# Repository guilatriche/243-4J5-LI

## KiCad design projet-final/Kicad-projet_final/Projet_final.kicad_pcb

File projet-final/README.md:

# Projet Final : Infrastructure de Télémétrie - Poste 07 (Centrale Thermique)
**Cours 243-4J5-LI | Hydro-Limoilou**

## 📖 Contexte du Projet
Ce projet simule le déploiement de l'infrastructure de télémétrie pour **Hydro-Limoilou**. L'objectif est de surveiller les conditions opérationnelles (climat, sécurité, alimentation) de 8 sites de distribution d'énergie. 

Le **Poste 07**, simulant une **Centrale Thermique**, est responsable de son propre répéteur RF, de ses capteurs, de son courtier MQTT local (Raspberry Pi 5) et de son écran de monitoring tactile. Un serveur central (VM gérée par l'enseignant) agrège les données via une convention de topics standardisée.

---

## 🛠️ Matériel & Capteurs
- **Contrôleur Principal** : LilyGO T-SIM7600G-H (ESP32 avec modem LTE)
- **Interface Tactile** : Raspberry Pi 5 + Écran officiel 7"
- **Capteurs (I2C)** :
  - **BME280** : Température, Humidité et Pression atmosphérique.
  - **BH1750** : Intensité lumineuse (Lux) pour détection d'intrusion.
- **Sécurité (GPIO)** :
  - **Capteur PIR** : Détection de mouvement infrarouge.
- **Actuateurs** :
  - 2 LEDs de statut (Contrôlables via MQTT).

---

## 📐 Conception Matérielle (PCB)
Le shield PCB pour l'ESP32 a été conçu sous KiCad pour assurer une connectivité fiable et robuste des capteurs.

### Livrables de Conception (Dossier `/kicad`)
- **Schéma Électrique** : `shield.kicad_sch` (Validé par ERC)
- **Design du PCB** : `shield.kicad_pcb` (Validé par DRC, 2 couches)
- **Fichiers de Fabrication** : Dossier incluant les **Gerbers** (RS-274X) et le **BOM** (Bill of Materials).

### Consultation Rapide (Dossier `/docs`)
- **Schéma de principe** : [schéma_électrique.pdf](./docs/schéma_électrique.pdf)
- **Vue du montage** : [Photo_breadboard.jpeg](./docs/Photo_breadboard.jpeg)
- **Vidéo du scénario 1 - Démonstration de l'installation** : [Scénario_1_Présentation.MP4](./docs/Scénario%201%20-%20Présentation.MP4)
- **Vidéo du scénario 2 - Démonstration des alarmes** : [Scénario_2_Alarmes.MP4](./docs/Scénario%202%20-%20Alarmes.MP4)
- **Vidéo du scénario 3 - Démonstration du lien de secours** : [Scénario_3_Lien de secours.MP4](./docs/Scénario%203%20-%20Lien%20de%20secours.MP4)

---

## 🔌 Schéma de Câblage & Connexions
Le nœud capteur utilise un LilyGO T-SIM7600G-H. Voici l'assignation des broches (Pinout) utilisée pour le montage :

### 1. Bus I2C (Capteurs environnementaux)
*Partagé entre le BME280 et le BH1750 (Adresses 0x76 et 0x23).*
- **SDA** : GPIO 21
- **SCL** : GPIO 22
- **VCC** : 3.3V
- **GND** : Ground

### 2. Sécurité & Indicateurs
- **Capteur PIR (Mouvement)** : GPIO 32 (Entrée digitale)
- **LED 1 (Statut)** : GPIO 14 (Sortie via résistance 220Ω)
- **LED 2 (Alerte)** : GPIO 13 (Sortie via résistance 220Ω)

### 3. Gestion Énergie & Modem (Interne LilyGO)
- **Batterie ADC** : GPIO 35 (Pont diviseur interne pour mesure de tension)
- **Modem TX/RX** : GPIO 26 / 27
- **Modem Power Key** : GPIO 4
- **Board Power On** : GPIO 12 (Doit être HIGH pour alimenter les périphériques)

---

## 🚀 Fonctionnalités Clés

- **Surveillance & IA** : Publication des données environnementales et génération d'un diagnostic technique en langage naturel (IA LLM Groq) toutes les 2 minutes.
- **Sécurité Temps Réel** : Alarmes critiques (mouvement et intrusion porte) publiées en moins de 1 seconde avec QoS 1.
- **Connectivité Hybride** : Basculement automatique (Failover) entre le WiFi (Lien principal) et le réseau LTE (Lien de secours WAN privé).
- **Interface IHM** : HUD Pygame tactile sur le Pi 5 avec gestion des alarmes (verrouillage visuel et acquittement manuel).

---

## 🛠 Architecture MQTT & Contrat de Données

Le système respecte strictement la convention de topics de Hydro-Limoilou. Tous les topics sont obligatoirement préfixés par : `hydro-limoilou/poste-07/`.

| Catégorie | Topic (Suffixe) | QoS | Rétention | Description |
| :--- | :--- | :--- | :--- | :--- |
| **Télémétrie** | `telemetry/{capteur}` | 0 | Non | Mesures périodiques (10s) |
| **Statut** | `status` | 0 | Oui | État du nœud (Uptime, RSSI, Batterie) |
| **Statut IA** | `status/llm` | 0 | Oui | Diagnostic généré par l'IA (120s) |
| **Alarmes** | `alarm/{type}` | 1 | Non | Évènements : `motion`, `door` |
| **Actuateurs**| `actuators/{nom}` | 0 | Non | Commandes descendantes (VM → site) |

### 📊 Format des Payloads (JSON)
Les payloads sont minifiés et incluent obligatoirement un timestamp Unix.
- **Télémétrie** : `{"value": 22.4, "unit": "C", "ts": 1778526188}`
- **Alarmes** : `{"level": "critical", "value": 2500, "unit": "lux", "ts": 1778526188}`
- **Statut** : `{"uptime": 3600, "rssi": -67, "link": "wifi", "battery_v": 3.92, "ts": 1778526188}`

---

## 🔒 Exposition & Sécurité
Le courtier Mosquitto local du Pi 5 est accessible au serveur central via un **Tunnel Cloudflare** sécurisé.

- **URL de connexion** : `wss://mqtt.gretier.xyz:443/mqtt`
- **Username** : `central`
- **Password** : `<TRANSMIS_VIA_CANAL_SECURISE>` (Identifiants restreints par ACL)
- **Contrôle d'Accès (ACL)** : L'utilisateur central dispose d'un accès en **lecture seule** sur le site, sauf pour le dossier `/actuators/` où l'écriture est permise.

---

## 🧪 Procédure de Démonstration (Scénarios de Test)

### Scénario 1 : Fonctionnement Nominal -> **RÉSULTAT : PASSÉ ✅**
1.  Démarrer l'ESP32 et l'interface tactile.
2.  Vérifier sur l'interface que les jauges de température et humidité se mettent à jour toutes les 10 secondes.
3.  Confirmer sur le tableau de bord central (VM) la réception des données avec le bon `site-id`.

### Scénario 2 : Déclenchement d'Alarme -> **RÉSULTAT : PASSÉ ✅**
1.  Simuler une intrusion en passant la main devant le capteur PIR ou en éclairant brusquement le BH1750.
2.  **Résultat attendu** : L'interface tactile passe immédiatement en mode alerte (clignotement rouge). Un message avec `QoS 1` est publié sur `alarm/motion` ou `alarm/door`.
3.  Appuyer sur le bouton **ACQUITTER** sur l'écran tactile pour rétablir l'état normal.

### Scénario 3 : Perte et Reprise de Lien -> **RÉSULTAT : PASSÉ ✅**
1.  Brancher le câble Ethernet reliant le Pi 5 au serveur de la VM.
2.  Sur l'interface tactile (Page **LINK**), appuyer sur le bouton **PASSER AU WAN PRIVÉ**.
3.  **Résultat attendu** : L'interface se déconnecte du Cloud et se reconnecte instantanément au lien local (`ws://192.168.100.7:9001`). Le champ "Broker" et "Réseau" sur l'écran se mettent à jour.
4.  Appuyer sur **PASSER AU CLOUD** pour revenir au mode de fonctionnement nominal.

---

## 📦 Installation & Déploiement

### Configuration des Secrets
Le projet utilise un fichier de configuration unique pour le firmware et l'interface afin d'éviter la duplication des identifiants et sécuriser le dépôt.
1.  **Copiez** le fichier modèle : `cp firmware/auth.h.example firmware/auth.h`.
2.  **Éditez** `firmware/auth.h` avec vos vrais identifiants (WiFi, MQTT, API Groq).
3.  Le script Python dans `/interface` chargera automatiquement ces valeurs via le module `config_loader.py`.

### Firmware (LilyGO ESP32)
1.  Compilez et téléversez :
    ```bash
    arduino-cli compile --fqbn esp32:esp32:esp32 firmware/firmware.ino
    arduino-cli upload -p /dev/ttyUSB0 --fqbn esp32:esp32:esp32 firmware/firmware.ino
    ```

### Interface (Raspberry Pi)
1.  Installez les dépendances : `pip install pygame paho-mqtt`.
2.  Lancez l'interface :
    ```bash
    python3 interface/interface.py
    ```

## 📝 Auteurs
Projet final réalisé dans le cadre du laboratoire Hydro-Limoilou par l'étudiant responsable du Poste 07.

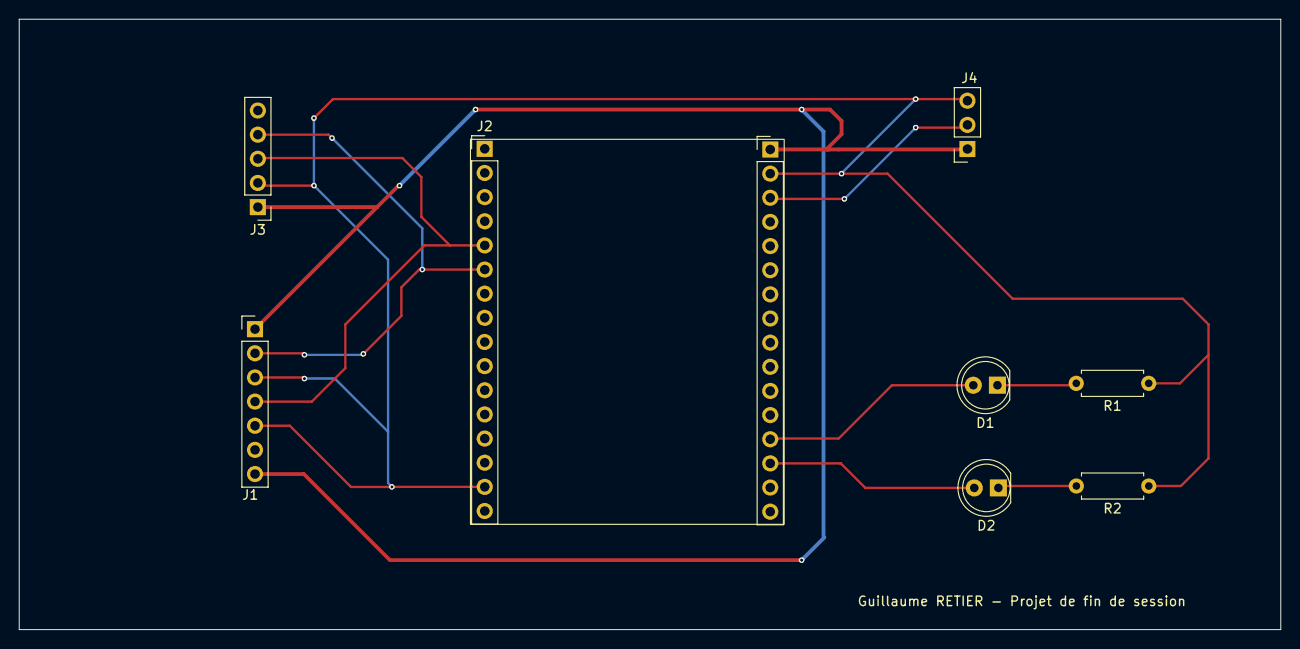
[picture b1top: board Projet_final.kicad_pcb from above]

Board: 2 copper layers, 132.7 x 64.2 mm, 8 parts (0 on the bottom side), 9 nets.

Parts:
D1: LED_VERTE; LED_D5.0mm
D2: LED_ROUGE; LED_D5.0mm
J1: BME820; BME280
J2: Lilygo LTE; header lyligo
J3: BH1750; Capteur de lumière
J4: EKMC4607112K; PinHeader PIR
R1, R2: 330; R_Axial_DIN0207_L6.3mm_D2.5mm_P7.62mm_Horizontal

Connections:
+3.3V: J1.1, J1.7, J2.17, J3.1, J4.1
GND: J1.3, J1.5, J2.15, J2.18, J3.2, J4.3, R1.1, R2.1
unnamed: D1.2 (A), J2.29
unnamed: D1.1 (K), R1.2
unnamed: D2.2 (A), J2.30
unnamed: D2.1 (K), R2.2
unnamed: J1.2, J2.6, J3.4
unnamed: J1.4, J2.5, J3.3
unnamed: J2.19, J4.2

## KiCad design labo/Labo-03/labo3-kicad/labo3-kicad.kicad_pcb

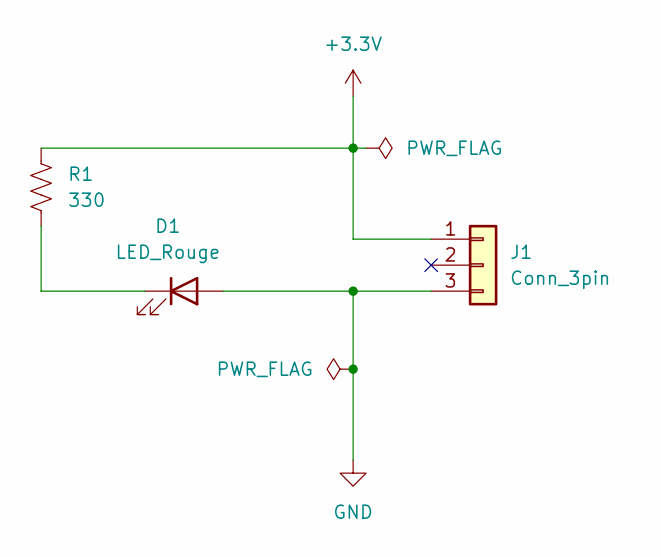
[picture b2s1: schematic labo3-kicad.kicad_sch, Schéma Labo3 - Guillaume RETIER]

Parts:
D1: LED_Rouge; LED_0805_2012Metric
J1: Conn_3pin; FanPinHeader_1x03_P2.54mm_Vertical
R1: 330; R_0805_2012Metric

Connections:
+3.3V: J1.1, R1.1
GND: D1.2 (A), J1.3
unnamed: D1.1 (K), R1.2

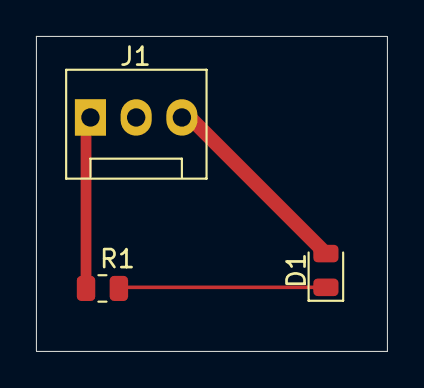
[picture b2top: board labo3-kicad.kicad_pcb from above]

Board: 2 copper layers, 19.5 x 17.5 mm, 3 parts (0 on the bottom side), 3 nets.

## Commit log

2026-02-03 Ajout de fonctionnalité via Opencode: bouton REBOOT avec message de confirmation
2026-02-04 Ajout du contrôle de LEDs via interface tactile et port série
2026-02-05 Interface tactile Curses fonctionnelle avec contrôle des LEDs
2026-02-05 Add simplified touch UI with two large buttons (Red/Green)
2026-02-05 Code Arduino validé pour le pilotage des LEDs 13 et 15
2026-02-19 Finalisation Labo 02 : Interface MQTT et sécurisation des secrets
2026-02-26 Labo 3 - KICAD terminé
    Labo 3 terminé
2026-03-12 Projet de mi-session
2026-03-12 modification topologie
2026-03-26 feat: initial release of Kessel Run IoT project
2026-03-26 Ajout de la photo du protoboard
2026-03-26 Captures des interfaces du jeu
2026-03-26 docs: enrich root README with GPIO mapping, photos, and project navigation
2026-03-26 balance: divide asteroid collision damage by 5
2026-04-02 Labo 4 - Appel LLM du Lilygo T-Beam SupremeOutil externe
2026-04-19 Projet LLM
2026-04-19 Schéma modifié
2026-04-30 Checkpoint: Version stable restaurée et fonctionnelle
2026-04-30 Backup: Version fonctionnelle avec détection de mouvement (PIR)
2026-04-30 Initial commit: Firmware de base avec support MQTT et correctif LED_02
2026-04-30 Securite : Retrait des fichiers sensibles du suivi Git
2026-04-30 Nettoyage : Retrait du dossier backups du suivi Git
2026-04-30 Structure : Organisation complète du répertoire projet-final (firmware, interface, kicad, docs)
2026-04-30 Schéma électrique
2026-04-30 Photo du breadboard
2026-05-11 feat: centralize configuration, finalize documentation and secure sensitive data
2026-05-11 feat: add manual broker switch for demo scenario
2026-05-14 Ajout dossier KICAD
2026-05-18 Ajout de la vidéo scénario 1
2026-05-18 Ajout de la vidéo scénario 2
2026-05-18 Ajout de la vidéo scénario 3
2026-05-18 Add demonstration videos to README
2026-05-18 Rename video files in README for consistency
2026-05-18 Fix video link encoding in README.md
2026-05-18 Update video links in README for scenarios 2 and 3
2026-05-18 Add rule to ignore KiCad automatic backups
2026-05-24 Create test
